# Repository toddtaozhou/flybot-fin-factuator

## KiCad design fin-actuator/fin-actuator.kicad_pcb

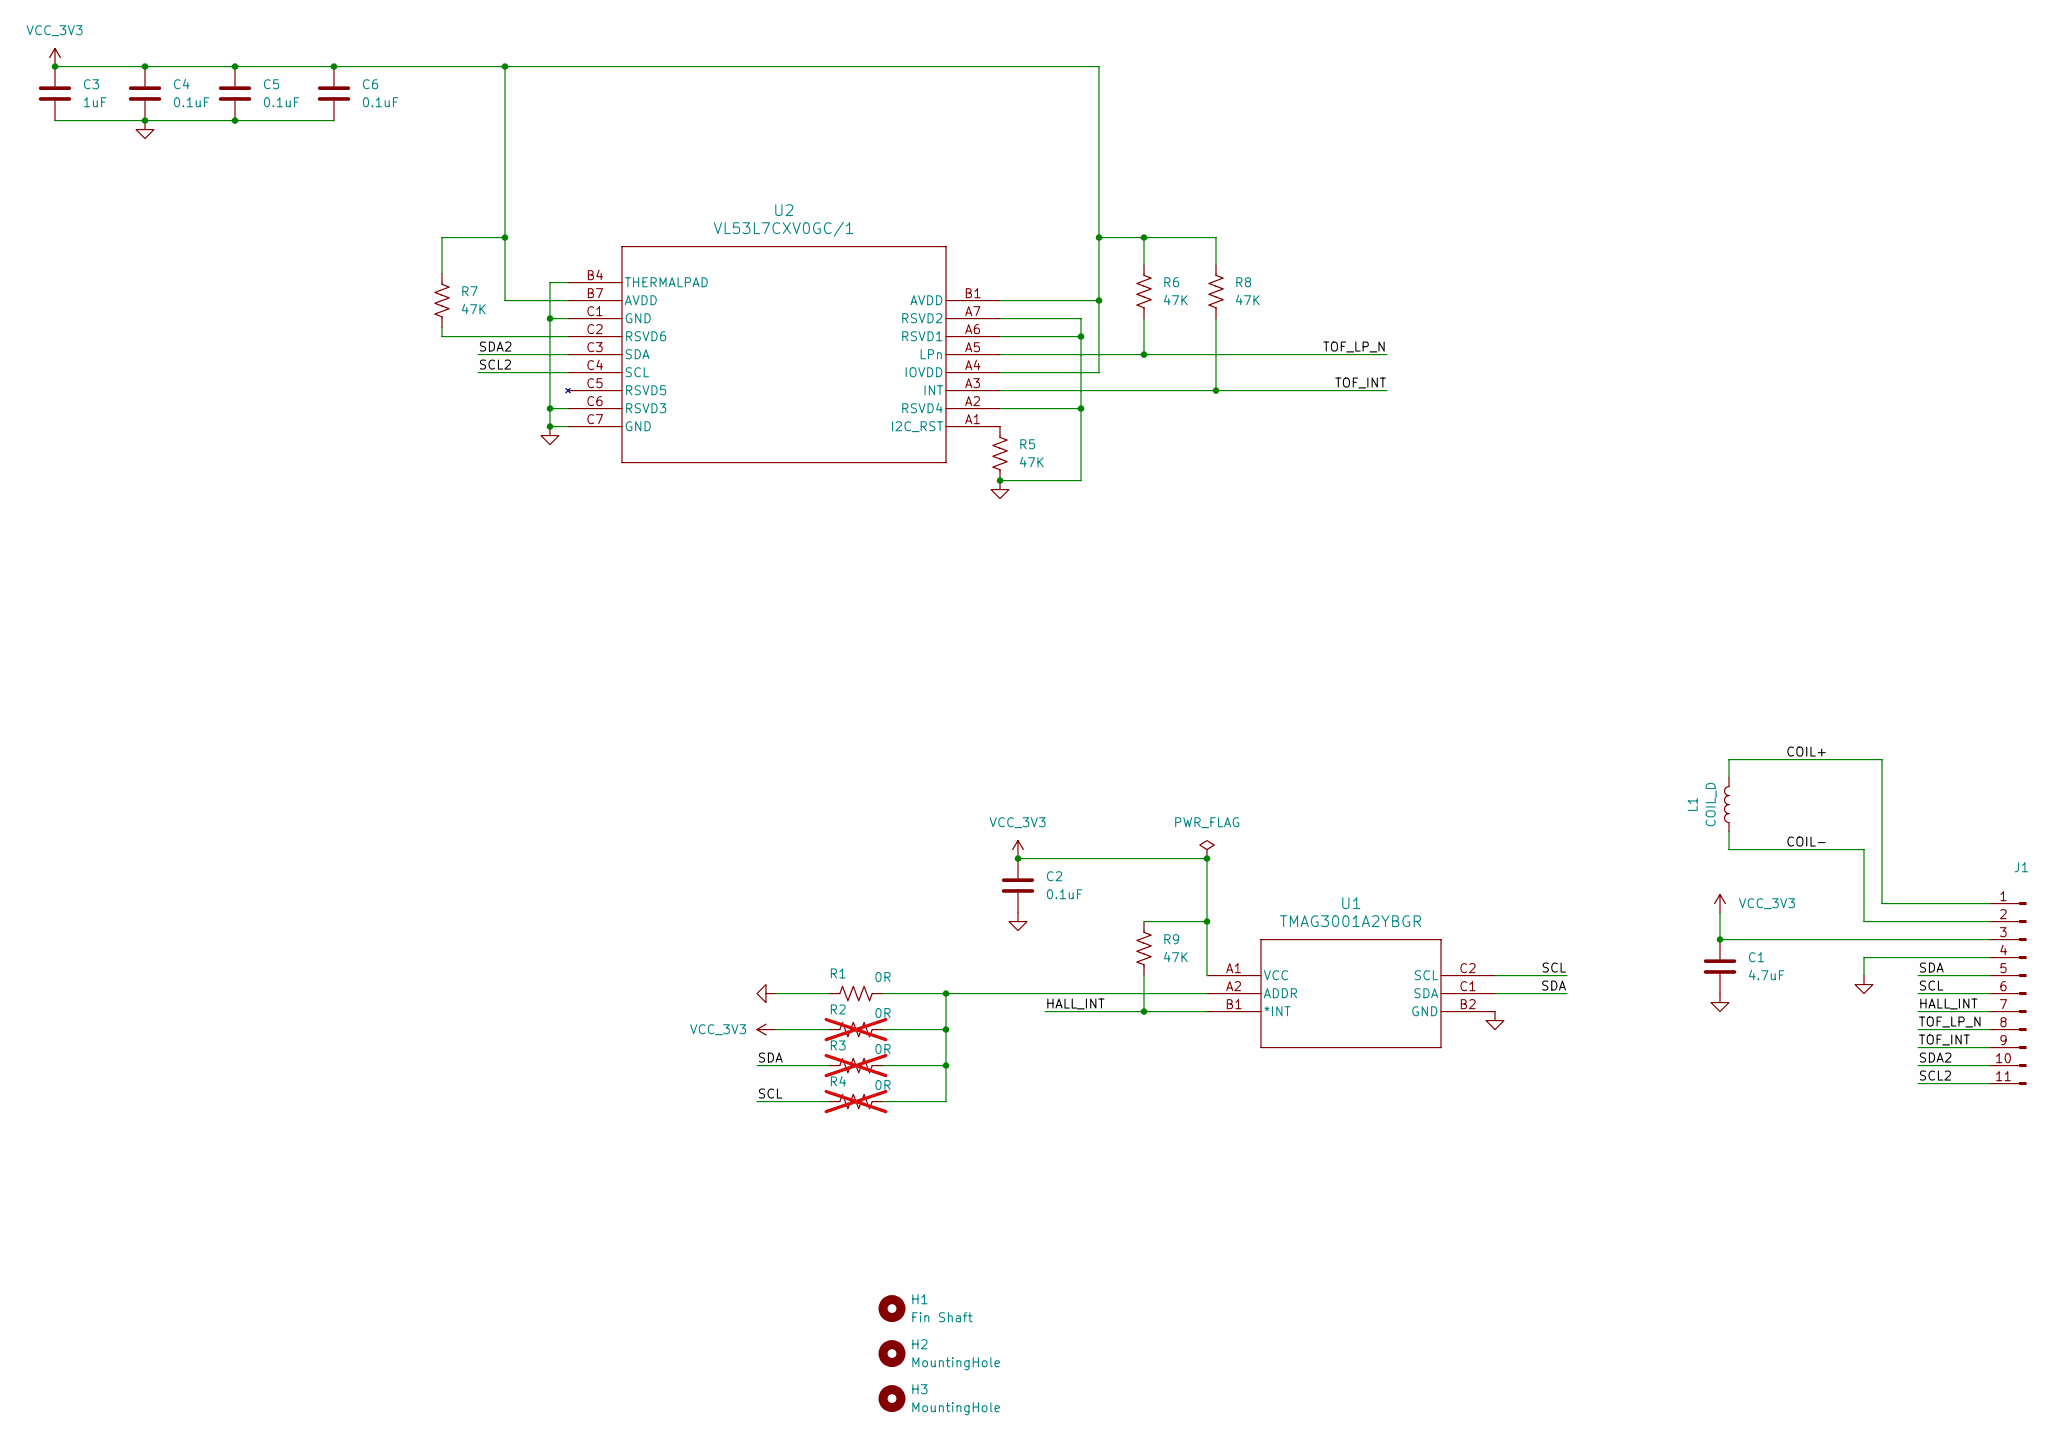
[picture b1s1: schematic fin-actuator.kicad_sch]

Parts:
C1: 4.7uF; C_0603_1608Metric
C2, C4, C5, C6: 0.1uF; C_0402_1005Metric
C3: 1uF; C_0402_1005Metric
H1: Fin Shaft; FIN_MOUNT_HOLE
H2, H3: MountingHole; MOUNTING_HOLE
J1: Conn_01x11_Pin; FIN_CONN_COIL_11
L1: COIL_D; COIL_6X6
R1: 0R; R_0201_0603Metric
R2, R3, R4: 0R; R_0201_0603Metric; not fitted
R5, R6, R7, R8, R9: 47K; R_0402_1005Metric
U1: TMAG3001A2YBGR; DSBGA6_YBG_TEX-L
U2: VL53L7CXV0GC/1; LGA16_OPTICAL-LINER_STM

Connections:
/COIL+: J1.1, L1.1
/COIL-: J1.2, L1.2
/HALL_INT: J1.7, R9.2, U1.B1 (*INT)
/SCL: J1.6, R4.1, U1.C2 (SCL)
/SCL2: J1.11, U2.C4 (SCL)
/SDA: J1.5, R3.1, U1.C1 (SDA)
/SDA2: J1.10, U2.C3 (SDA)
/TOF_INT: J1.9, R8.2, U2.A3 (INT)
/TOF_LP_N: J1.8, R6.2, U2.A5 (LPn)
GND: C1.2, C2.2, C3.2, C4.2, C5.2, C6.2, J1.4, R1.1, R5.2, U1.B2 (GND), U2.A2 (RSVD4), U2.A6 (RSVD1), U2.A7 (RSVD2), U2.B4 (THERMALPAD), U2.C1 (GND), U2.C6 (RSVD3), U2.C7 (GND)
unnamed: R1.2, R2.2, R3.2, R4.2, U1.A2 (ADDR)
unnamed: R5.1, U2.A1 (I2C_RST)
unnamed: R7.2, U2.C2 (RSVD6)
VCC_3V3: C1.1, C2.1, C3.1, C4.1, C5.1, C6.1, J1.3, R2.1, R6.1, R7.1, R8.1, R9.1, U1.A1 (VCC), U2.A4 (IOVDD), U2.B1 (AVDD), U2.B7 (AVDD)

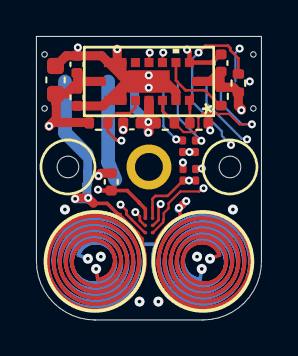
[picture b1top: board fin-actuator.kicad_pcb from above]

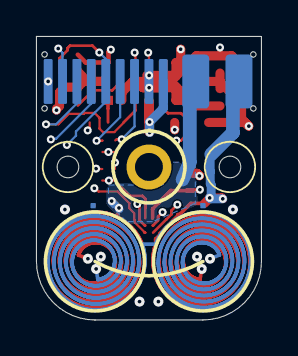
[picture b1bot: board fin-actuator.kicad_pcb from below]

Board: 6 copper layers, 12.5 x 15.8 mm, 22 parts (2 on the bottom side), 14 nets.

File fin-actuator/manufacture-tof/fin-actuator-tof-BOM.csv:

"Reference","Qty","Value","DNP","Exclude from BOM","Exclude from Board","Footprint"
"C1","1","4.7uF","","","","Capacitor_SMD:C_0603_1608Metric"
"C2,C4,C5,C6","4","0.1uF","","","","Capacitor_SMD:C_0402_1005Metric"
"C3","1","1uF","","","","Capacitor_SMD:C_0402_1005Metric"
"J1","1","Conn_01x11_Pin","","","","flybot:FIN_CONN_COIL_11"
"R1","1","0R","","","","Resistor_SMD:R_0201_0603Metric"
"R2,R3,R4","3","0R","DNP","","","Resistor_SMD:R_0201_0603Metric"
"R5,R6,R7,R8,R9","5","47K","","","","Resistor_SMD:R_0402_1005Metric"
"U1","1","TMAG3001A2YBGR","","","","TMAG3001A2YBGR:DSBGA6_YBG_TEX-L"
"U2","1","VL53L7CXV0GC/1","","","","VL53L7CXV0GC_1:LGA16_OPTICAL-LINER_STM"
